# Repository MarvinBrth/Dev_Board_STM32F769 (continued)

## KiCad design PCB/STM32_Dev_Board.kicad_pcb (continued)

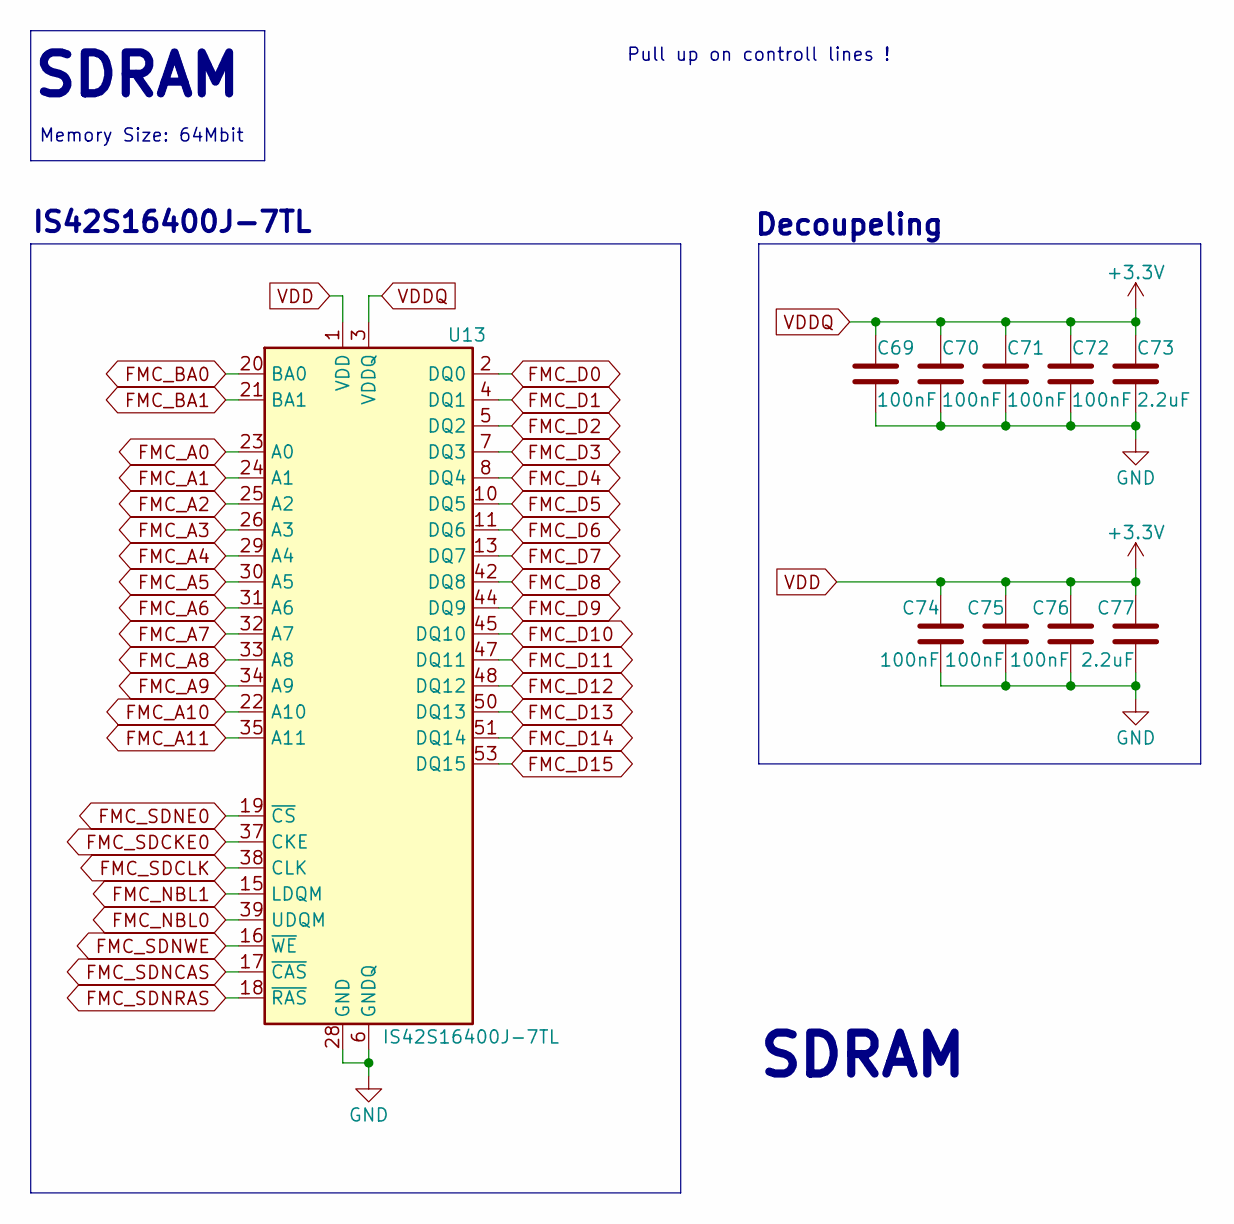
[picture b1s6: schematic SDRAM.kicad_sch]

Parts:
C69, C70, C71, C72, C74, C75, C76: 100nF; C_0402_1005Metric
C73, C77: 2.2uF; C_0603_1608Metric
U13: IS42S16400J-7TL; TSOP-II-54_22.2x10.16mm_P0.8mm

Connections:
FMC_A0: U13.23 (A0); also elsewhere on the board
FMC_A1: U13.24 (A1); also elsewhere on the board
FMC_A2: U13.25 (A2); also elsewhere on the board
FMC_A3: U13.26 (A3); also elsewhere on the board
FMC_A4: U13.29 (A4); also elsewhere on the board
FMC_A5: U13.30 (A5); also elsewhere on the board
FMC_A6: U13.31 (A6); also elsewhere on the board
FMC_A7: U13.32 (A7); also elsewhere on the board
FMC_A8: U13.33 (A8); also elsewhere on the board
FMC_A9: U13.34 (A9); also elsewhere on the board
FMC_A10: U13.22 (A10); also elsewhere on the board
FMC_A11: U13.35 (A11); also elsewhere on the board
FMC_BA0: U13.20 (BA0); also elsewhere on the board
FMC_BA1: U13.21 (BA1); also elsewhere on the board
FMC_D0: U13.2 (DQ0); also elsewhere on the board
FMC_D1: U13.4 (DQ1); also elsewhere on the board
FMC_D2: U13.5 (DQ2); also elsewhere on the board
FMC_D3: U13.7 (DQ3); also elsewhere on the board
FMC_D4: U13.8 (DQ4); also elsewhere on the board
FMC_D5: U13.10 (DQ5); also elsewhere on the board
FMC_D6: U13.11 (DQ6); also elsewhere on the board
FMC_D7: U13.13 (DQ7); also elsewhere on the board
FMC_D8: U13.42 (DQ8); also elsewhere on the board
FMC_D9: U13.44 (DQ9); also elsewhere on the board
FMC_D10: U13.45 (DQ10); also elsewhere on the board
FMC_D11: U13.47 (DQ11); also elsewhere on the board
FMC_D12: U13.48 (DQ12); also elsewhere on the board
FMC_D13: U13.50 (DQ13); also elsewhere on the board
FMC_D14: U13.51 (DQ14); also elsewhere on the board
FMC_D15: U13.53 (DQ15); also elsewhere on the board
FMC_NBL0: U13.39 (UDQM); also elsewhere on the board
FMC_NBL1: U13.15 (LDQM); also elsewhere on the board
FMC_SDCKE0: U13.37 (CKE); also elsewhere on the board
FMC_SDCLK: U13.38 (CLK); also elsewhere on the board
FMC_SDNCAS: U13.17 (~CAS); also elsewhere on the board
FMC_SDNE0: U13.19 (~CS); also elsewhere on the board
FMC_SDNRAS: U13.18 (~RAS); also elsewhere on the board
FMC_SDNWE: U13.16 (~WE); also elsewhere on the board
GND: C69.2, C70.2, C71.2, C72.2, C73.2, C74.2, C75.2, C76.2, C77.2, U13.6 (GNDQ), U13.12 (GNDQ), U13.28 (GND), U13.41 (GND), U13.46 (GNDQ), U13.52 (GNDQ), U13.54 (GND); also elsewhere on the board
VDDSDMMC_STM32: C69.1, C70.1, C71.1, C72.1, C73.1, C74.1, C75.1, C76.1, C77.1, U13.1 (VDD), U13.3 (VDDQ), U13.9 (VDDQ), U13.14 (VDD), U13.27 (VDD), U13.43 (VDDQ), U13.49 (VDDQ); also elsewhere on the board

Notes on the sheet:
Decoupeling
Pull up on controll lines !
Memory Size: 64Mbit
SDRAM
IS42S16400J-7TL

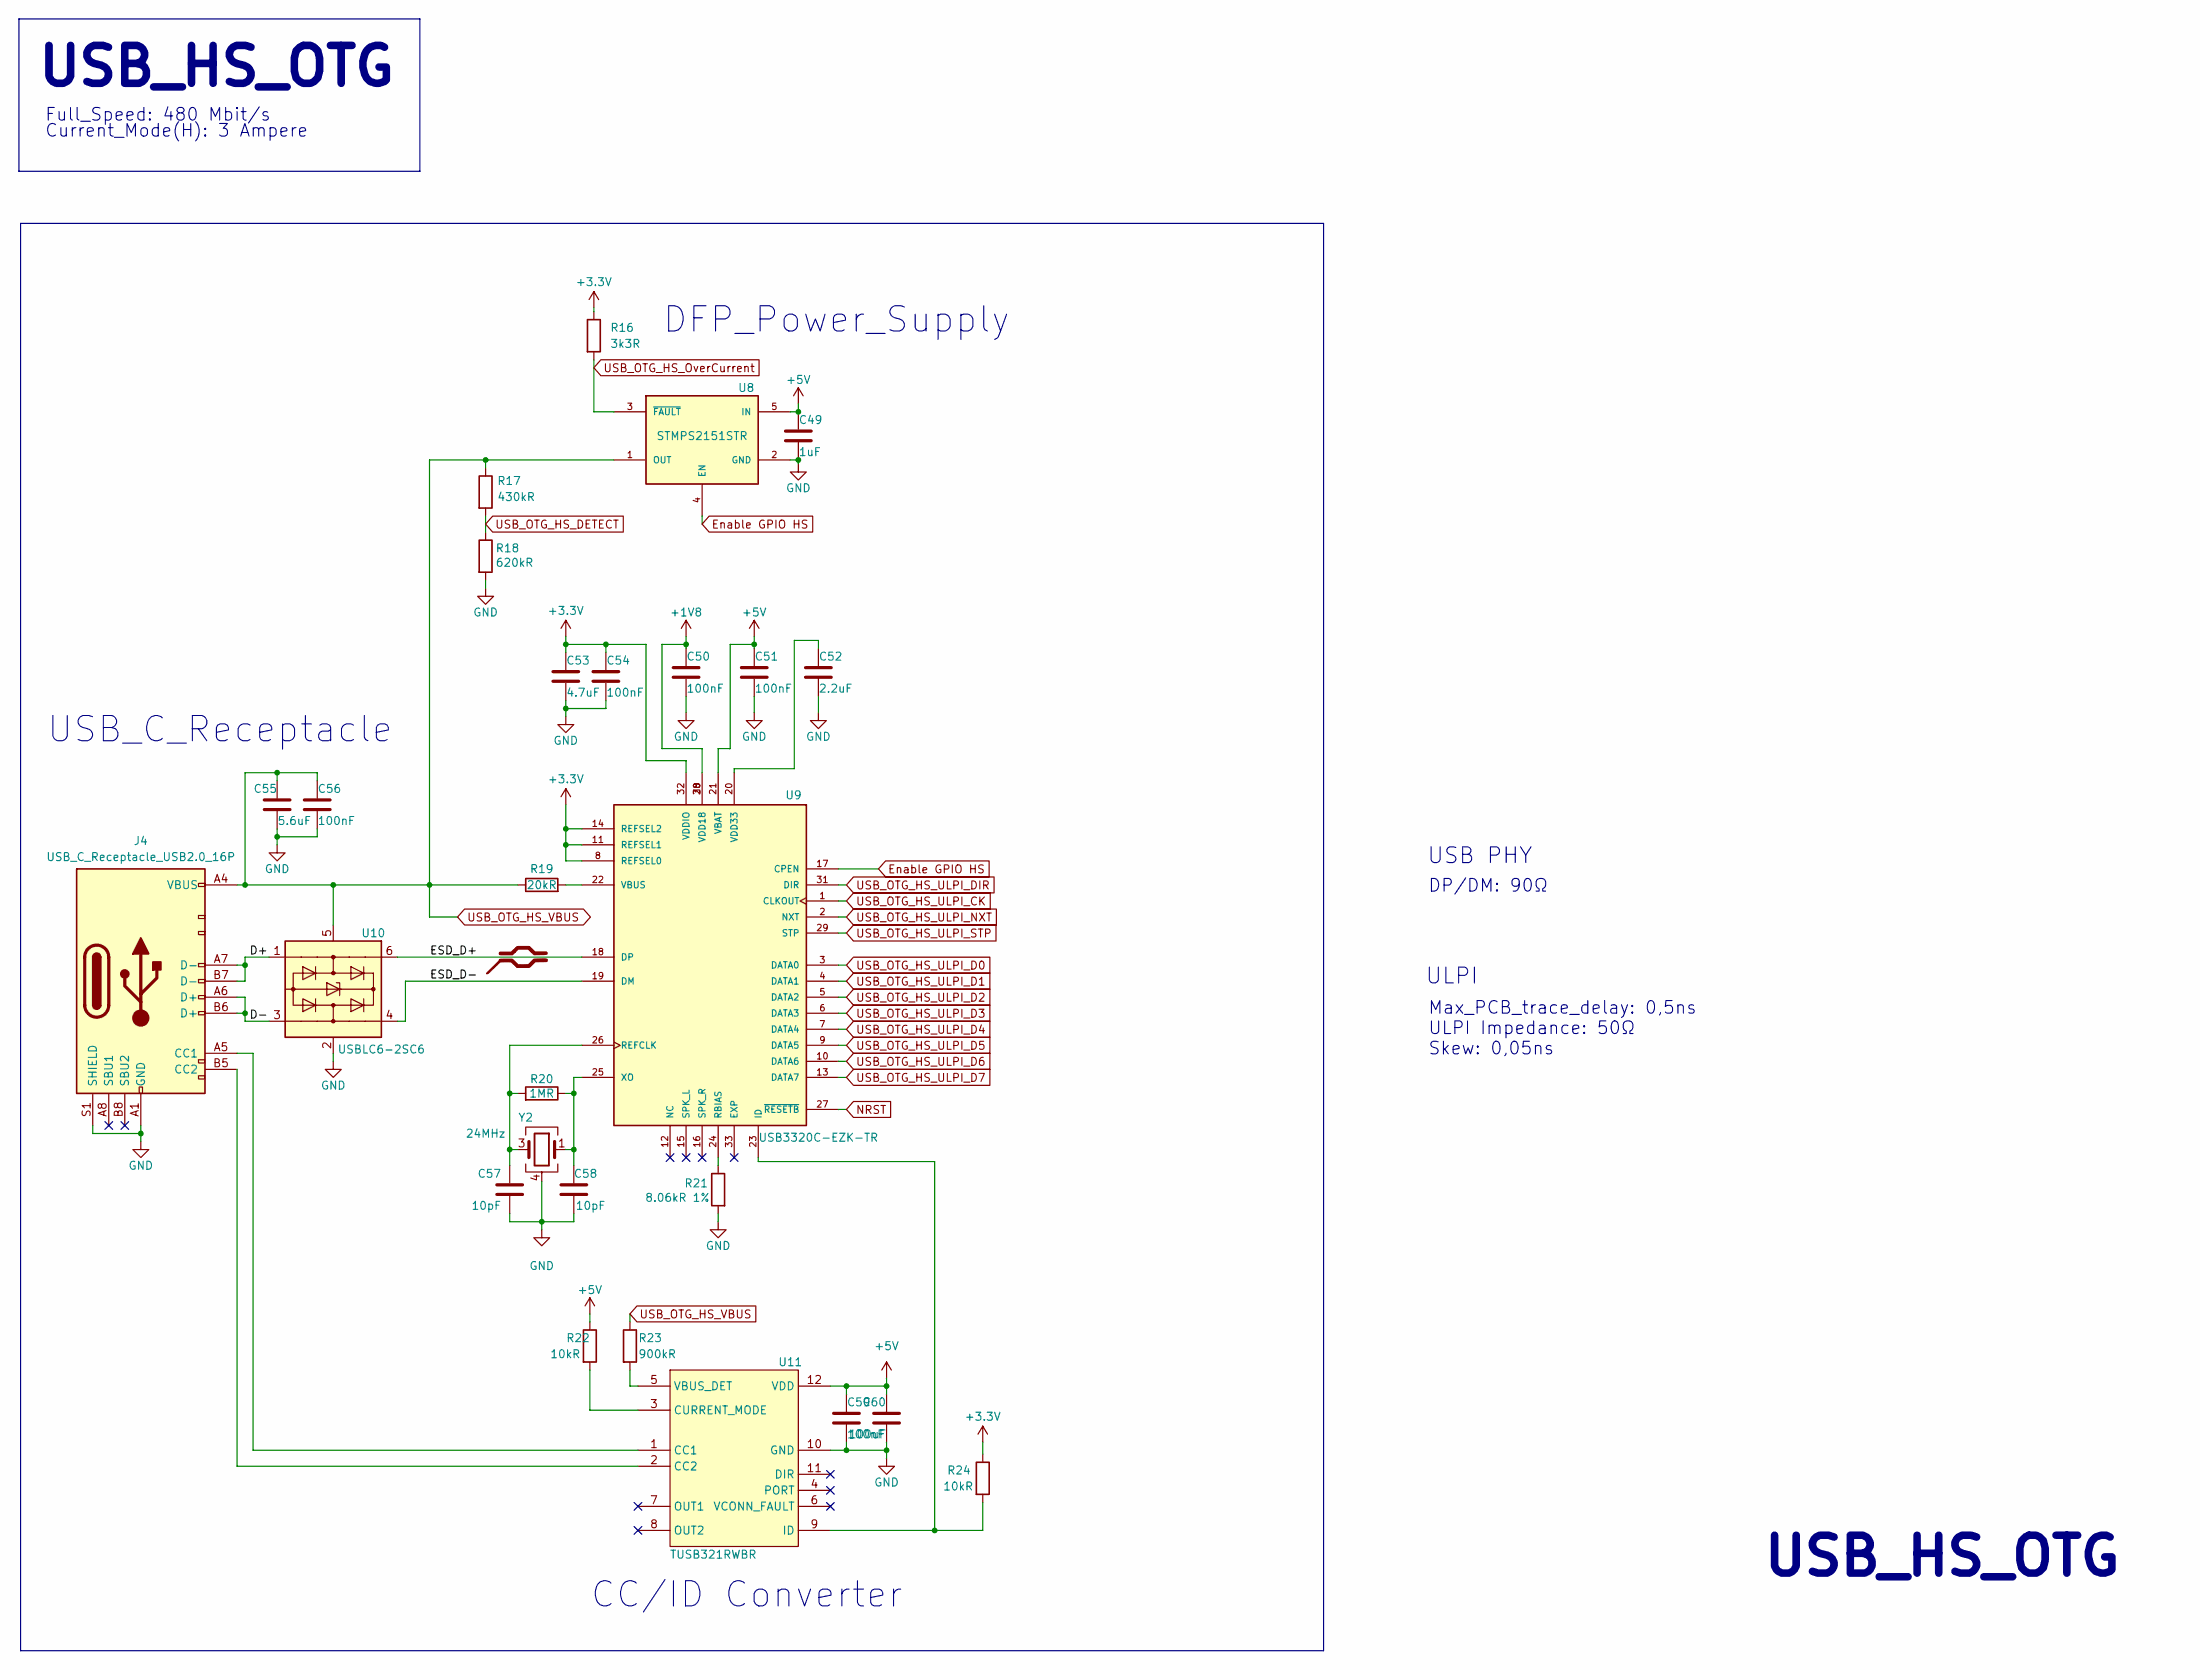
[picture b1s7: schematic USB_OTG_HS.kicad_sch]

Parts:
C49: 1uF; C_0603_1608Metric
C50, C51, C54, C56, C59: 100nF; C_0402_1005Metric
C52: 2.2uF; C_0402_1005Metric
C53: 4.7uF; C_0402_1005Metric
C55: 5.6uF; C_0603_1608Metric
C57, C58: 10pF; C_0402_1005Metric
C60: 100uF; C_0805_2012Metric
J4: USB_C_Receptacle_USB2.0_16P; GT-USB-7047B_JLCPCB
R16: 3k3R; R_0402_1005Metric
R17: 430kR; R_0402_1005Metric
R18: 620kR; R_0402_1005Metric
R19: 20kR; R_0402_1005Metric
R20: 1MR; R_0402_1005Metric
R21: 8.06kR 1%; R_0402_1005Metric
R22, R24: 10kR; R_0402_1005Metric
R23: 900kR; R_0402_1005Metric
U8: STMPS2151STR; STMPS; PARTREV 7
U9: USB3320C-EZK-TR; USB_ULPI
U10: USBLC6-2SC6; SOT-23-6
U11: TUSB321RWBR
Y2: 24MHz; XTAL_ECS-240-10-36-CKM-TR

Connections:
+1V8: C50.1, U9.28 (VDD18), U9.30 (VDD18); also elsewhere on the board
+5V: C49.1, C51.1, C59.1, C60.1, R22.1, U8.5 (IN), U9.21 (VBAT), U11.12 (VDD); also elsewhere on the board
/USB_OTG_HS/D+: J4.A7 (D-), J4.B7 (D-), U10.1 (I/O1)
/USB_OTG_HS/D-: J4.A6 (D+), J4.B6 (D+), U10.3 (I/O2)
/USB_OTG_HS/ESD_D+: U9.18 (DP), U10.6 (I/O1)
/USB_OTG_HS/ESD_D-: U9.19 (DM), U10.4 (I/O2)
Enable GPIO HS: U8.4 (EN), U9.17 (CPEN); also elsewhere on the board
GND: C49.2, C50.2, C51.2, C52.2, C53.2, C54.2, C55.2, C56.2, C57.2, C58.2, C59.2, C60.2, J4.A1 (GND), J4.A12 (GND), J4.B1 (GND), J4.B12 (GND), J4.S1 (SHIELD), R18.2, R21.2, U8.2 (GND), U10.2 (GND), U11.10 (GND), Y2.2, Y2.4; also elsewhere on the board
NRST: U9.27 (~RESETB); also elsewhere on the board
unnamed: J4.A5 (CC1), U11.1 (CC1)
unnamed: J4.B5 (CC2), U11.2 (CC2)
unnamed: R21.1, U9.24 (RBIAS)
unnamed: C57.1, R20.2, U9.26 (REFCLK), Y2.3
unnamed: R19.2, U9.22 (VBUS)
unnamed: C52.1, U9.20 (VDD33)
unnamed: C58.1, R20.1, U9.25 (XO), Y2.1
unnamed: R22.2, U11.3 (CURRENT_MODE)
unnamed: R24.2, U9.23 (ID), U11.9 (ID)
unnamed: R23.2, U11.5 (VBUS_DET)
USB_OTG_HS_DETECT: R17.2, R18.1; also elsewhere on the board
USB_OTG_HS_OverCurrent: R16.2, U8.3 (~FAULT); also elsewhere on the board
USB_OTG_HS_ULPI_CK: U9.1 (CLKOUT); also elsewhere on the board
USB_OTG_HS_ULPI_D0: U9.3 (DATA0); also elsewhere on the board
USB_OTG_HS_ULPI_D1: U9.4 (DATA1); also elsewhere on the board
USB_OTG_HS_ULPI_D2: U9.5 (DATA2); also elsewhere on the board
USB_OTG_HS_ULPI_D3: U9.6 (DATA3); also elsewhere on the board
USB_OTG_HS_ULPI_D4: U9.7 (DATA4); also elsewhere on the board
USB_OTG_HS_ULPI_D5: U9.9 (DATA5); also elsewhere on the board
USB_OTG_HS_ULPI_D6: U9.10 (DATA6); also elsewhere on the board
USB_OTG_HS_ULPI_D7: U9.13 (DATA7); also elsewhere on the board
USB_OTG_HS_ULPI_DIR: U9.31 (DIR); also elsewhere on the board
USB_OTG_HS_ULPI_NXT: U9.2 (NXT); also elsewhere on the board
USB_OTG_HS_ULPI_STP: U9.29 (STP); also elsewhere on the board
USB_OTG_HS_VBUS: C55.1, C56.1, J4.A4 (VBUS), J4.A9 (VBUS), J4.B4 (VBUS), J4.B9 (VBUS), R17.1, R19.1, R23.1, U8.1 (OUT), U10.5 (VBUS); also elsewhere on the board
VDDSDMMC_STM32: C53.1, C54.1, R16.1, R24.1, U9.8 (REFSEL0), U9.11 (REFSEL1), U9.14 (REFSEL2), U9.32 (VDDIO); also elsewhere on the board

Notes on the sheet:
Max_PCB_trace_delay: 0,5ns ULPI Impedance: 50Ω Skew: 0,05ns
USB_C_Receptacle
USB_HS_OTG
Current_Mode(H): 3 Ampere
Full_Speed: 480 Mbit/s
DP/DM: 90Ω
CC/ID Converter
ULPI
DFP_Power_Supply
USB PHY

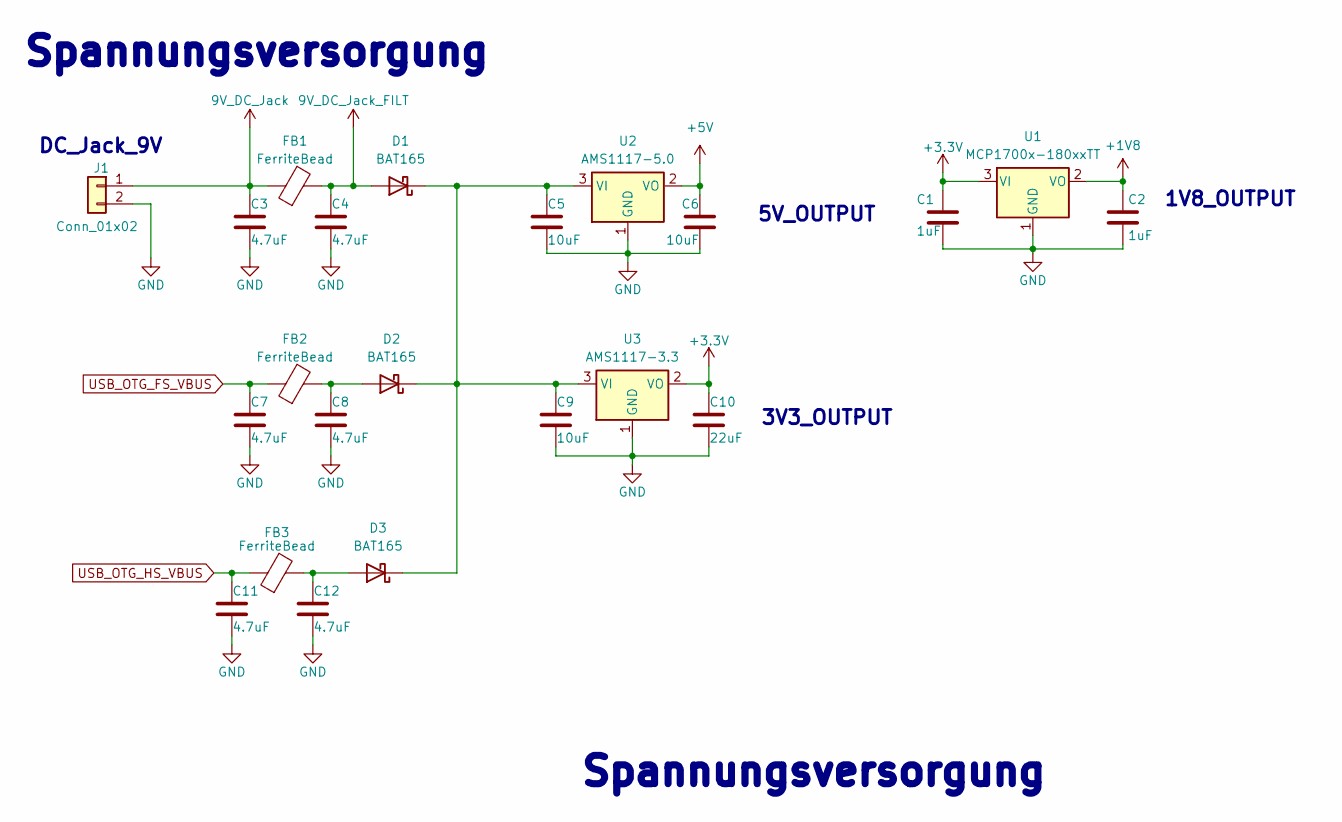
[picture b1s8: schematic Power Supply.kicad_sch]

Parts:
C1, C2: 1uF; C_0603_1608Metric
C3, C4, C7, C8, C11, C12: 4.7uF; C_0805_2012Metric
C5, C6, C9: 10uF; C_0805_2012Metric
C10: 22uF; C_0805_2012Metric
D1, D2, D3: BAT165
FB1, FB2, FB3: FerriteBead; L_0603_1608Metric
J1: Conn_01x02; JST_XH_B2B-XH-A_1x02_P2.50mm_Vertical
U1: MCP1700x-180xxTT; SOT-23
U2: AMS1117-5.0; SOT-223-3_TabPin2
U3: AMS1117-3.3; SOT-223-3_TabPin2

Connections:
9V_DC_Jack: C3.1, FB1.1, J1.1; also elsewhere on the board
9V_DC_Jack_FILT: C4.1, D1.2, FB1.2
+1V8: C2.1, U1.2 (VO); also elsewhere on the board
+5V: C6.1, U2.2 (VO); also elsewhere on the board
GND: C1.2, C2.2, C3.2, C4.2, C5.2, C6.2, C7.2, C8.2, C9.2, C10.2, C11.2, C12.2, J1.2, U1.1 (GND), U2.1 (GND), U3.1 (GND); also elsewhere on the board
unnamed: C8.1, D2.2, FB2.2
unnamed: C12.1, D3.2, FB3.2
unnamed: C5.1, C9.1, D1.1, D2.1, D3.1, U2.3 (VI), U3.3 (VI)
USB_OTG_FS_VBUS: C7.1, FB2.1; also elsewhere on the board
USB_OTG_HS_VBUS: C11.1, FB3.1; also elsewhere on the board
VDDSDMMC_STM32: C1.1, C10.1, U1.3 (VI), U3.2 (VO); also elsewhere on the board

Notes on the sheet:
1V8_OUTPUT
Spannungsversorgung
3V3_OUTPUT
5V_OUTPUT
DC_Jack_9V

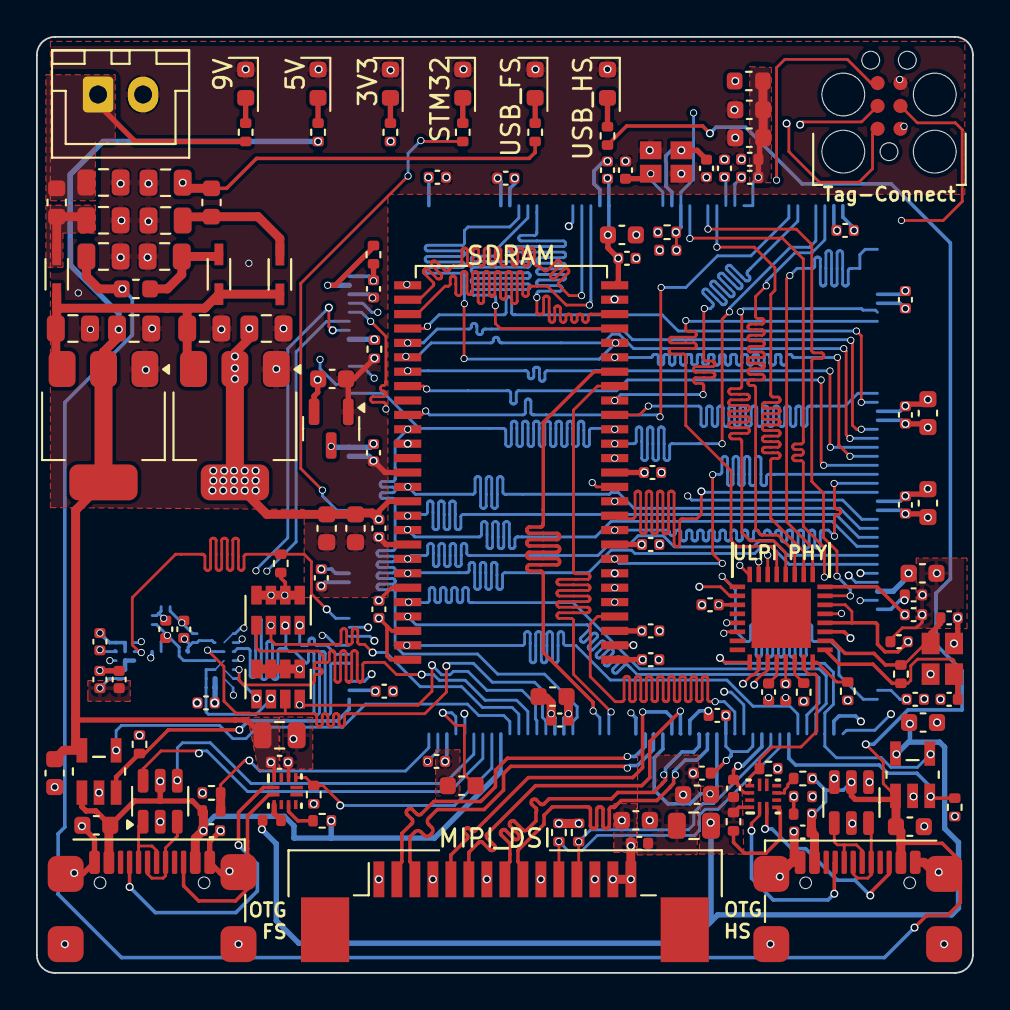
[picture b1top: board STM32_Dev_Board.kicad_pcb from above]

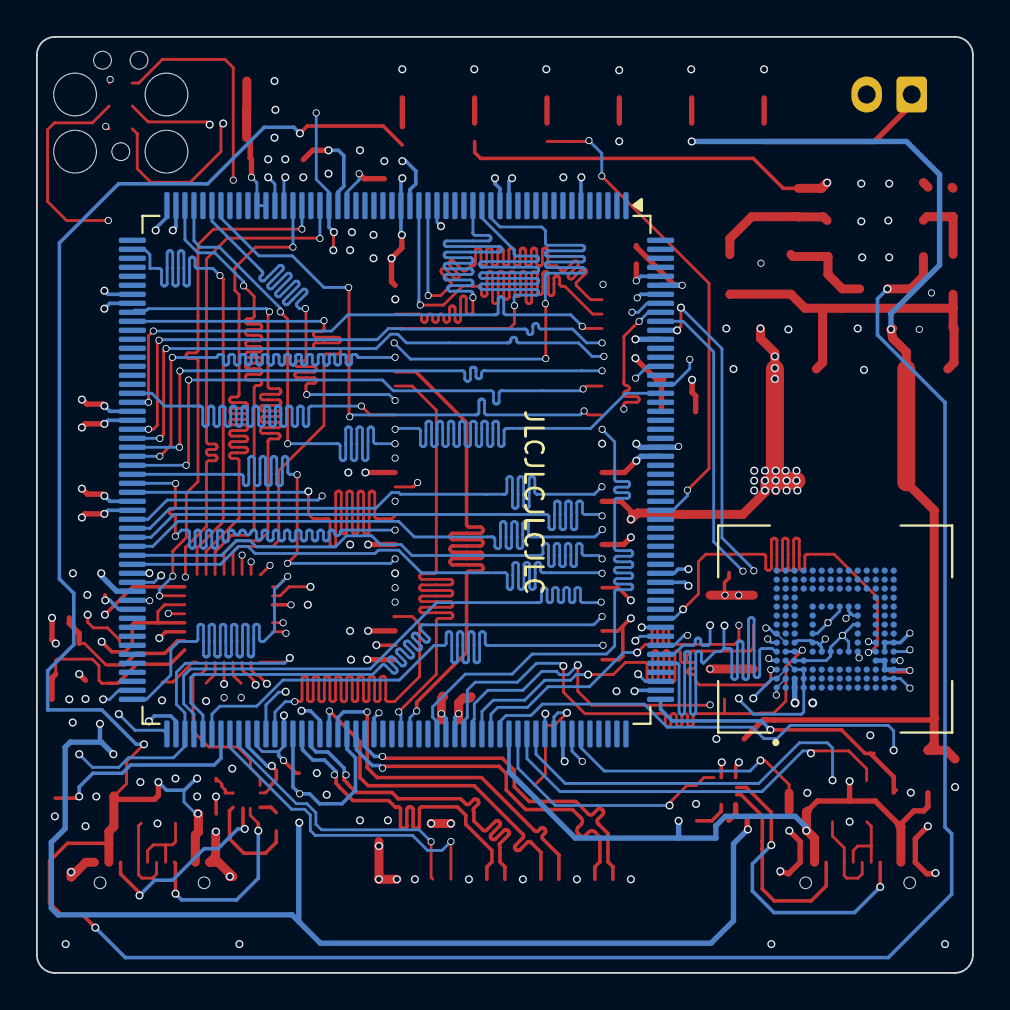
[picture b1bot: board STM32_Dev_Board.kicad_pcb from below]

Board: 6 copper layers, 52.0 x 52.0 mm, 139 parts (2 on the bottom side), 128 nets.

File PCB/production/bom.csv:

Designator,Footprint,Quantity,Value,LCSC Part #
"C1, C2, C35, C37, C44, C49",0603,6,1uF,
C10,0805,1,22uF,
"C11, C12, C3, C4, C7, C8",0805,6,4.7uF,
"C13, C14, C15, C16, C17, C18, C19, C20, C21, C22, C23, C24, C25, C26, C27, C28, C30, C31, C34, C36, C41, C46, C47, C50, C51, C54, C56, C59, C61, C64, C66, C68, C69, C70, C71, C72, C74, C75, C76",0402,39,100nF,
"C29, C32, C33, C67",0603,4,4.7uF,
"C38, C42, C43, C73, C77",0603,5,2.2uF,
"C39, C40, C57, C58",0402,4,10pF,
"C45, C55",0603,2,5.6uF,
"C48, C60",0805,2,100uF,
"C5, C6, C9",0805,3,10uF,
C52,0402,1,2.2uF,
"C53, C62, C65",0402,3,4.7uF,
C63,0402,1,1uF,
"D1, D2, D3",BAT165,3,BAT165,
"D4, D5, D6, D7, D8, D9",0603,6,LED,
"FB1, FB2, FB3, FB4",0603,4,FerriteBead,
J1,JST_XH_B2B-XH-A_1x02_P2.50mm_Vertical,1,Conn_01x02,
"J3, J4",GT-USB-7047B_JLCPCB,2,USB_C_Receptacle_USB2.0_16P,
J5,TE_1-84952-5_1x15-1MP_P1.0mm_Horizontal,1,Conn_01x15,
"R1, R13, R15, R2, R22, R24, R25, R3",0402,8,10kR,
"R10, R16",0402,2,3k3R,
"R11, R17",0402,2,430kR,
"R12, R18",0402,2,620kR,
"R14, R23",0402,2,900kR,
R19,0402,1,20kR,
R20,0402,1,1MR,
R21,0402,1,8.06kR 1%,
"R26, R27",Widerstandsarray_1,2,10kR,
"R28, R29",0402,2,1.5kR,
R4,0402,1,5kR,
"R5, R8",0402,2,330R,
"R6, R7, R9",0402,3,1kR,
U1,SOT-23,1,MCP1700x-180xxTT,
"U10, U6",SOT-23-6,2,USBLC6-2SC6,
"U11, U7",TUSB321RWBR,2,TUSB321RWBR,
U12,EMMC,1,EMMC64G-IY29-5B101,
U13,TSOP-II-54_22.2x10.16mm_P0.8mm,1,IS42S16400J-7TL,
U2,SOT-223-3_TabPin2,1,AMS1117-5.0,
U3,SOT-223-3_TabPin2,1,AMS1117-3.3,
U4,LQFP-208_28x28mm_P0.5mm,1,STM32F769BIT6,
"U5, U8",STMPS,2,STMPS2151STR,
U9,USB_ULPI,1,USB3320C-EZK-TR,
Y1,XTAL_ECS-240-10-36-CKM-TR,1,26MHz,
Y2,XTAL_ECS-240-10-36-CKM-TR,1,24MHz,

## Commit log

2024-08-07 Create keep
